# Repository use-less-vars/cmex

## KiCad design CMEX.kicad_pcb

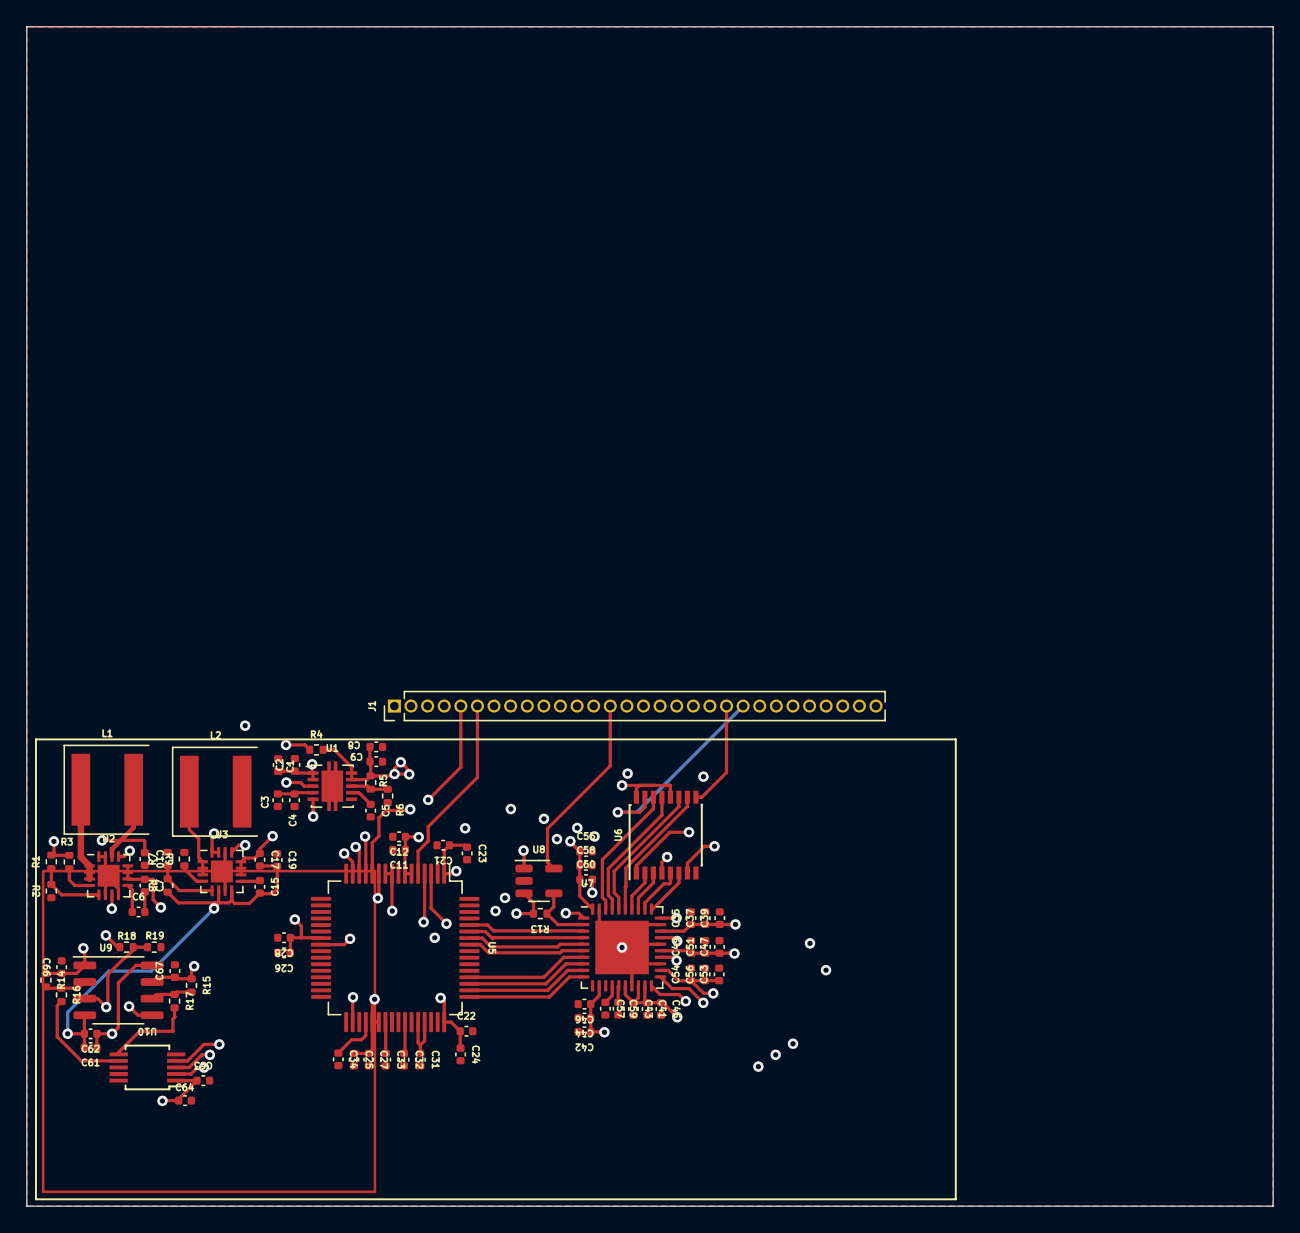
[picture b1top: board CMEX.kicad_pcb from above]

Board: 8 copper layers, 95.3 x 90.2 mm, 81 parts (0 on the bottom side), 72 nets.

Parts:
C1, C3, C8, C12, C23, C24, C27, C28, C39, C45, C46, C51, C56, C57, C59, C60, C62, C64, C66, C67: C0402_100nF_50V; C_0402_1005Metric
C2, C4, C9: C0402_4.7uF_6.3V; C_0402_1005Metric
C5: C0402_560p_10V; C_0402_1005Metric
C6, C15: C0402_330p_25V; C_0402_1005Metric
C7, C17, C31, C32: C0402_10uF_6.3V; C_0402_1005Metric
C10, C19: C0402_22uF_6.3V; C_0402_1005Metric
C11, C21, C22, C25, C26, C33, C34, C37, C43, C44, C49, C54, C58, C61, C63: C0402_1uF_6.3V; C_0402_1005Metric
C35, C41, C42, C47, C53, C55: C0402_10nF_16V; C_0402_1005Metric
J1: Conn_01x30; PinHeader_1x30_P1.27mm_Vertical
L1, L2: 2.2uH; L_Coilcraft_XAL60xx_6.36x6.56mm
R1: R0402_215k; R_0402_1005Metric
R2: R0402_150k; R_0402_1005Metric
R3, R9: R0402_100k; R_0402_1005Metric
R4: R0402_105k; R_0402_1005Metric
R5: R0402_6.19k; R_0402_1005Metric
R6: R0402_4.99k; R_0402_1005Metric
R7: R0402_120k; R_0402_1005Metric
R8: R0402_22k; R_0402_1005Metric
R13: R0402_100; R_0402_1005Metric
R14, R15, R19: R0402_33k; R_0402_1005Metric
R16, R17: R0402_10k; R_0402_1005Metric
R18: R0402_56k; R_0402_1005Metric
U1: TPS74801; VSON-10-1EP_3x3mm_P0.5mm_EP1.65x2.4mm
U2, U3: TPS62151; VQFN-16-1EP_3x3mm_P0.5mm_EP1.68x1.68mm
U5: ADS8584S; LQFP-64_10x10mm_P0.5mm
U6: SSOP-16_4.4x5.2mm_P0.65mm
U7: HVQFN-40-1EP_6x6mm_P0.5mm_EP4.1x4.1mm
U8: SOT-23-5
U9: TLC2272; SO-8_3.9x4.9mm_P1.27mm
U10: MCP4728-E_UN; MSOP-10_3x3mm_P0.5mm

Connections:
1V8a: C8.1, C9.1, C35.1, C37.1, C39.1, C41.1, C42.1, C43.1, C44.1, C45.1, C46.1, C47.1, C49.1, C51.1, C53.1, C54.1, C56.1, R4.2, R5.1, U1.9 (OUT), U1.10 (OUT), U7.12 (VDDD), U7.16 (VDDA), U7.18 (VDDA), U7.19 (VDDD), U7.22 (VDDA), U7.25 (VDDA), U7.28 (VDDA)
3V3: C11.1, C12.1, C26.1, C28.1, C55.1, C58.1, C60.1, C63.1, C64.1, J1.29, R18.2, U5.6 (nPAR/SER/BYTE_SEL), U5.7 (nSTBY), U5.23 (DVDD), U5.34 (REFSEL), U6.4 (G), U6.12 (nG), U6.16 (VCC), U7.40 (V3io), U8.1 (VCC), U10.1 (VDD)
5V: C7.1, C17.1, C21.1, C22.1, C23.1, C24.1, C25.1, C27.1, C61.1, C62.1, J1.30, U2.10 (AVIN), U2.11 (PVIN), U2.12 (PVIN), U3.10 (AVIN), U3.11 (PVIN), U3.12 (PVIN), U5.1 (AVDD), U5.37 (AVDD), U5.38 (AVDD), U5.48 (AVDD), U9.8 (+)
-5V: C15.2, C17.2, C19.2, C61.2, C62.2, R8.1, U3.6 (AGND), U3.8 (DEF), U3.15 (PGND), U3.16 (PGND), U9.4 (-)
/ADC/BUSY: J1.11, U5.14 (BUSY)
/ADC/CONV: J1.7, U5.9 (CONVSTA), U5.10 (CONVSTB)
/ADC/DATA: J1.12, U5.24 (DB7)
/ADC/FIRST: J1.13, U5.15 (FRSTDATA)
/ADC/OS0: J1.4, U5.3 (OS0)
/ADC/OS1: J1.5, U5.4 (OS1)
/ADC/OS2: J1.6, U5.5 (OS2)
/ADC/OUT0_M: U5.50 (AIN_1GND), U7.9 (OUT0_M)
/ADC/OUT0_P: U5.49 (AIN_1P), U7.10 (OUT0_P)
/ADC/OUT1_M: U5.52 (AIN_2GND), U7.7 (OUT1_M)
/ADC/OUT1_P: U5.51 (AIN_2P), U7.8 (OUT1_P)
/ADC/OUT2_M: U5.58 (AIN_3GND), U7.5 (OUT2_M)
/ADC/OUT2_P: U5.57 (AIN_3P), U7.6 (OUT2_P)
/ADC/OUT3_M: U5.60 (AIN_4GND), U7.3 (OUT3_M)
/ADC/OUT3_P: U5.59 (AIN_4P), U7.4 (OUT3_P)
/ADC/RST: J1.9, U5.11 (RESET)
/ADC/SCLK: J1.8, U5.12 (nRD/SCLK)
/ADC/~CS: J1.10, U5.13 (nCS)
/AWAGS/ADI_M: U6.10 (3Y), U7.35 (DI_M)
/AWAGS/ADI_P: U6.11 (3Z), U7.36 (DI_P)
/AWAGS/AIN0: J1.15, U7.21 (IN0)
/AWAGS/AIN1: J1.16, U7.24 (IN1)
/AWAGS/AIN2: J1.17, U7.27 (IN2)
/AWAGS/AIN3: J1.18, U7.30 (IN3)
/AWAGS/DO_M: R13.1, U7.2 (DO_M), U8.4 (B)
/AWAGS/DO_P: R13.2, U7.1 (DO_P), U8.3 (A)
/AWAGS/RST_M: U6.13 (4Z), U7.37 (RESET_M)
/AWAGS/RST_P: U6.14 (4Y), U7.38 (RESET_M)
/AWAGS/SCLK_M: U6.6 (2Y), U7.31 (SCLK_M)
/AWAGS/SCLK_P: U6.5 (2Z), U7.32 (SCLK_P)
/AWAGS/SEL_M: U6.3 (1Z), U7.33 (SEL_M)
/AWAGS/SEL_P: U6.2 (1Y), U7.34 (SEL_P)
/AWAGS/iADI: J1.21, U6.9 (3A)
/AWAGS/iADO0: J1.14, U8.5 (R)
/AWAGS/iCLK: J1.20, U6.7 (2A)
/AWAGS/iRST: J1.22, U6.15 (4A)
/AWAGS/iSEL: J1.19, U6.1 (1A)
/DAC/1V2: R18.1, R19.2, U9.3 (+), U9.5 (+)
/DAC/DAC_REF_X: R17.2, U10.6 (VOUTA)
/DAC/DAC_REF_Y: R16.2, U10.7 (VOUTB)
/DAC/SCL_DAC_REF: J1.23, U10.2 (SCL)
/DAC/SDA_DAC_REF: J1.24, U10.3 (SDA)
/DAC/VBIAS1: C67.1, J1.27, R15.1, U9.7
/DAC/VBIAS2: C66.1, J1.26, R14.1, U9.1
/DAC/~LDAC_DAC_REF: J1.25, U10.4 (~LDAC)
/Power_suppy/2V: C1.1, C2.1, C10.1, L1.2, R1.2, R3.2, U1.1 (IN), U1.2 (IN), U1.5 (EN), U2.7 (FSW), U2.14 (VOS)
/Power_suppy/ENABLE_PWR: J1.28, U2.13 (EN), U3.13 (EN)
GND: C1.2, C2.2, C3.2, C4.2, C5.2, C6.2, C7.2, C8.2, C9.2, C10.2, C11.2, C12.2, C19.1, C21.2, C22.2, C23.2, C24.2, C25.2, C26.2, C27.2, C28.2, C31.2, C32.2, C33.2, C34.2, C35.2, C37.2, C39.2, C41.2, C42.2, C43.2, C44.2, C45.2, C46.2, C47.2, C49.2, C51.2, C53.2, C54.2, C55.2, C56.2, C57.2, C58.2, C59.2, C60.2, C63.2, C64.2, C66.2, C67.2, J1.3, L2.2, R2.1, R6.1, R7.2, R9.2, R19.1, U1.6 (GND), U1.11 (THERM), U2.6 (AGND), U2.8 (DEF), U2.15 (PGND), U2.16 (PGND), U2.17 (THERM), U3.7 (FSW), U3.14 (VOS), U3.17 (THERM), U5.2 (AGND), U5.8 (RANGE), U5.26 (AGND), U5.33 (DB15/BYTE_SEL), U5.35 (AGND), U5.40 (AGND), U5.41 (AGND), U5.43 (REFGND), U5.46 (REFGND), U5.47 (AGND), U5.53 (AGND_passive), U5.54 (AGND_passive), U5.55 (AGND_passive), U5.56 (AGND_passive), U5.61 (AGND_passive), U5.62 (AGND_passive), U5.63 (AGND_passive), U5.64 (AGND_passive), U6.8 (GND), U7.11 (GND), U7.17 (GND), U7.20 (GNDD), U7.23 (GNDD), U7.26 (GNDD), U7.29 (GNDD), U7.39 (V0io/GND), U7.41 (Pad), U8.2 (GND), U10.10 (VSS)
unnamed: L1.1, U2.1 (SW), U2.2 (SW), U2.3 (SW)
unnamed: L2.1, U3.1 (SW), U3.2 (SW), U3.3 (SW)
unnamed: C3.1, C4.1, U1.4 (BIAS)
unnamed: R5.2, R6.2, U1.8 (FB)
unnamed: R4.1, U1.3 (PG)
unnamed: C5.1, U1.7 (SS)
unnamed: R1.1, R2.2, U2.5 (FB)
unnamed: R3.1, U2.4 (PG)
unnamed: C6.1, U2.9 (SS/TR)
unnamed: R7.1, R8.2, U3.5 (FB)
unnamed: R9.1, U3.4 (PG)
unnamed: C15.1, U3.9 (SS/TR)
unnamed: C31.1, U5.44 (REFCAPA), U5.45 (REFCAPB)
unnamed: C32.1, U5.42 (REFIN/REFOUT)
unnamed: C34.1, U5.36 (REGCAP1)
unnamed: C33.1, U5.39 (REGCAP2)
unnamed: C59.1, U7.15 (AUTO_SET)
unnamed: C57.1, U7.14 (DAC_SET)
unnamed: R14.2, R16.1, U9.2 (-)
unnamed: R15.2, R17.1, U9.6 (-)

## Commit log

2023-05-13 Added gitignore, and pro,sch,pcb-files
2023-06-29 Added two sub-sheets for power supply and adc. Started to make the power supply.
2023-06-29 Schaltplan für Spannungsversorgung angelegt.
2023-07-10 Added awags and dac sheet.
2023-07-11 Added DAC circuit.
2023-07-11 Changed power supply.
2023-07-11 Added negative power supply.
2023-07-12 Changed global to hierarchichal lables, reorganized main sheet to get pins to connector.
2023-07-12 Added connector to all sheets.
2023-07-13 Schematic finished, ready for review.
2023-09-16 Layout erster Entwurf fertig.
2023-09-21 Kleine Änderung.
